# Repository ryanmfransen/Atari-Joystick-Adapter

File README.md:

# Atari Joystick Adapter
A bluetooth adapter for the Atari CX-40 joysticks

## Finished Product

## Design Objectives
You might ask why I would build such a project. With the proliferation of existing gamepads, retro tech, and alternatives, what is it about this that makes it unique?

Fair question. To begin, let's roll back the clock. I used to have all the old systems, and when I wanted to play any of the retro machines, I would simply toss in the cartridge and play away, just like when I was a kid.

I've since sold my collection of retro game machines and recently got into emulation. Emulation affords me the opportunity to still play the old school games yet be able to do so on a single, modern appliance. 

This is great, except for one thing; The joysticks.

I miss playing games as they were intended. It just isn't the same thing playing Space Invaders on the Atari 2600 with the classic joystick as it is playing it on an emulator with a modern XBox controller.  Yes, it works fine, but the experience is not the same.

The Atari Joystick Adapter was born. *I wanted a way to use my classic joysticks the way the games were designed for while playing emulation.*
## Design Goals
**Classic Joysticks**

I wanted to be able to use my existing class joysticks without modification.

**Wireless**

The adapter needed to be wireless, so I can sit back on my couch and play games without being tethered to an appliance.

**Emulator Navigation**

I needed ther ability to navigater, and control the emulator with the classic joystick such that I could select, launch and play games without the use of another controller, remote, or keyboard.

**Additional Game System Buttons**

I needed the ability to mimic the buttons on the original Atari to begin playing games - Start for example.

**Battery Operated**

To be truly wireless, I needed to make this a battery operated device, and be able to charge the device simply by plugging in a USB-C cable such as is with modern rechargeable devices.

**Professional**

Yeah yeah I know, this is a one off device but I want it to look professional, with a custom PCB, and a good looking multicolour 3D printed enclosure.

## The PCB

I designed the circuit using KiCad. I designed most of the symbols, and footprints, sans the simple capacitor, resistor, and connectors. I think I also grabbed the ESP32 symbol from somewhere. The schematics and the KiCad project files can be found here: [Atari Joystick Adapter KiCad Project](kicad/)

Schematic:

Here is a 3d Render (v1.1):

Here is a picture of the populated board (v1.0)

I sent the gerber files to PCBWay to be built, and received 10 boards in about a week.

## Interfacing the Atari Joystick

The Atari joystick uses a simple mechanism to manage the four direction buttons and the fire button.  Each button is assigned to a pin on the connector, and when pressed brings the pin low, as is seen from the ground, or common pin on the connector, pin eight(8). This makes it quite easy to connect to the ESP32, all I needed was simple debounce circuits and can otherwise go straight into the digital GPIO pins.

## The Atari Connector

I recall back in the seventies and eighties we used to use standard DB9 serial connectors when we were making Atari style joysticks or interfacing to them. While these don't quite fit perfectly, they do work well. For this project I wanted to finally make use of real Atari joystick connectors, so I found a source for them in San Jose, Best Electronics, and bough 20 of them.

I've also modelled the Atari joystick connector in CAD.  Mostly just to help facilitate designing the enclosure for fitment, however I also added it to the KiCad footprint so you could also render the 3d model of the PCB with it as well.

You can download the model here: [Atari Joystick Connector Model](models/atarijoystickmodel.step)

## ESP32

I ended up using the ESP32 Mini WROOM-32 by KeeYees.  I really like the mini board configuration, as I have used several of the similar D1Minis ESP8266's in the past.

The ESP32 dev board was the obvious choice for this project as it has the bluetooth connectivity I need and sufficient GPIO pins.

I used this ESP32 from Amazon: [ESP32 Mini Wroom-32](https://www.amazon.ca/gp/product/B08TBQRMY4)

## Battery and Battery Charging

One of my design goals was to use a rechargeable battery and circuit.  I had a bunch of 18650 batteries around for other projects, so that seemed like it would be a good fit for this project.  I would have to settle on a charging circuit, and I could obtain a TC4056 Lithium Battery Charger Module Board from Amazon for quite cheap.  This would more than suffice for what I needed.  The ESP32 uses a 5V input, so I needed to deal with this, as the 18650 has a 3.7v output, which does diminish during it's charge/release cycle.  A simple DC-DC 6W Mini Step-Up Boost Converter would do the trick, and boost me up to 5V, regardless of the diminishing voltage. Perfect - Both these parts are cheap and easily available.

At this point all I had to do was throw a switch into the power circuit and that should solve my power requirements. Done.

I purchased this [Battery Charger](https://www.amazon.ca/gp/product/B0B48VWHTD) from Amazon

I purchased this [Boost Converter](https://www.amazon.ca/gp/product/B09TZSGHYK) from Amazon

## Enclosure

I designed the enclosure in Autodesk's Fusion 360. I think it worked out quite well.  The enclosure consists of the main(top) piece, and the cover (bottom) as well as three switch extensions so you can use the three switches placed in the PCB such that they would extend the proper amount up and out of the top case.

The enclosure CAD files can be found here: [Atari Joystick Adapter CAD Files](models)

The Bambu Studio .3mf file for the enclosure can be found here: [Atari Joystick Adapter Bambu Studio 3mf Project File](bambustudio/Atari%20Joystick%20Adapter%20Case.3mf)

## The Code

I built the code for this project in C++ using Visual Studio Code and PlatformIO, with the Arduino Framework.  I make use the GamepadBLE library by lemmingDEV, found here: [ESP-32-BLE-Gamepad](https://github.com/lemmingDev/ESP32-BLE-Gamepad)

I use a number of classes to manage the program.  The main class is the Button class.  The Button class encapsulates everything needed to support using buttons on your retro joysticks. It will store the current button state, whether the state has changed, which ESP32 GPIO pin the button is assigned to, and it handles the hardware interrupt callback for that button.  Each button manages it's own interup handler to encapsulate the interrupt logic. This class is used for the joystick, or d-pad (hat) direction buttons.

The second Class is the FireButton class, extending the Button class.  This adds in the addition of a button identifier, used for gamepad buttons, such as the fire button.

The interrupt service routines, in the button objects simply set the updated state, and flag the button as having changed state.

Managing the interrupt handler in each object is a handy way to control state. Most solutions I have seen out on Youtube have some sort of global variables storing the state for all the buttons.  I like the ability to do this atomically, it keeps things clean.

Here is the Button class initializer function, setting the ISR for the class instance.
```
void Button::init() {
  // Set the pin to input and use a pullup resistor
  pinMode(pin, INPUT_PULLUP);

  // Set the current state of the pin
  this->state = LOW;

  // Let's attach the interrupt handler
  std::function<void(void)> stdFunct {std::bind(&Button::instanceIsr, this)};
  attachInterrupt(digitalPinToInterrupt(this->pin), stdFunct, CHANGE);
}
```

The main loop of the application simply iterates over the button instances, checking if they have changed state.  If they have, then the new state is sent via the bluetooth gamepad.

The project code and all source files are included for you.

This project was built to accommodate the four joystick direction buttons, the single joystick fire button, as well as three additional buttons to support game system and emulator navigation and control.

The joystick direction buttons are mapped to the four hat buttons in the gamepad emulation.  The possible states are:

```
  LEFT_UP:8     UP:1          UP_RIGHT:2 
  ⎡    ▲    ⎤   ⎡    ▲    ⎤   ⎡    ▲    ⎤
  ⎢    0    ⎟   ⎢    0    ⎟   ⎢    0    ⎟
  ⎢◀︎ 0   1 ▷⎟   ⎢◁ 1   1 ▷⎟   ⎢◁ 1   0 ▶︎⎟
  ⎢    1    ⎟   ⎢    1    ⎟   ⎢    1    ⎟ 
  ⎣    ▽    ⎦   ⎣    ▽    ⎦   ⎣    ▽    ⎦ 
  
  LEFT:7        CENTERED:0    RIGHT:3
  ⎡    △    ⎤   ⎡    △    ⎤   ⎡    △    ⎤
  ⎢    1    ⎟   ⎢    1    ⎟   ⎢    1    ⎟
  ⎢◀︎ 0   1 ▷⎟   ⎢◁ 1   1 ▷⎟   ⎢◁ 1   0 ▶︎⎟
  ⎢    1    ⎟   ⎢    1    ⎟   ⎢    1    ⎟
  ⎣    ▽    ⎦   ⎣    ▽    ⎦   ⎣    ▽    ⎦
  
  DOWN_LEFT:6   DOWN:5        DOWN_RIGHT:4
  ⎡    △    ⎤   ⎡    △    ⎤   ⎡    △    ⎤
  ⎢    1    ⎟   ⎢    1    ⎟   ⎢    1    ⎟ 
  ⎢◀︎ 0   1 ▷⎟   ⎢◁ 1   1 ▷⎟   ⎢◁ 1   0 ▶︎⎟
  ⎢    0    ⎟   ⎢    0    ⎟   ⎢    0    ⎟
  ⎣    ▼    ⎦   ⎣    ▼    ⎦   ⎣    ▼    ⎦
```
Each state is mapped to an integer value, from `0..8` and it is this integer value sent to the gamepad controller to register the d-pad presses in the emulator.

The four buttons are buttons `1..4`, and are typically registered, depending on the system you pair with, as buttons a, b, x, y on the gamepad controller in the emulator.

From here, you can assign each of these four buttons to whatever makes sense for you.  I used:
```
[a], [b], [select], [start]
```

## Emulator

I use Retroarch, and it was a little tricky getting the proper button assignments configured so I could navigate the Retroarch menu, launch the game in the emulator, and then start the game, and play the game all with only using the Atari joystick and the buttons on the adapter.

Once configured, it works incredibly well.

## Did I achieve my Goals?

Yes! I believe so. Let's have a look:
- [x]  Classic Joysticks
- [x]  Wireless
- [x]  Emulator Navigation
- [x]  Additional Game System Buttons
- [x]  Battery Operated
- [x]  Professional

## Observations

1. Latency.  The latency is either incredible, or I am blind to it because I put so much effort into making this. In any event, gameplay is amazing, and very responsive.  I am very happy with the latency given the bluetooth connectivity, and emulation.

2. I actually use this.  Unlike most of my projects which are super fun to build, they usually end up on a shelf, or in a drawer, and I tend to forget about them. This project is different.  I actually is it, and is a lot of fun to play the games wit hthe classic controllers.

## What I Would do Different Next Time

1. Test Points. I would (and have in the v2 board) include test points to troubleshoot the circuit. This just makes things much easier to measure voltages and test your circuits.

2. Power Jumper. Ok, so I have to admit I placed all the parts, soldered everything in, and powered it on.  Of course, I forgot to configure the voltage booster from the default 12v to my required 5v, and I fried my brand new ESP32. 
 I've since added a two pin jumper that needs to be in place for the power to get to the ESP32, this way I can power the board up and test the circuit power without destroying the ESP.

3. My first prototype had the ESP32 soldered directly to the board, and while offers a nice finished product, see point 2 above, and I needed to remove it, so prototype two I put headers in and as you can see from the picture, the ESP32 is now removable, if ever needed.

4. While the 18650 works well, I might source a small flat pack lithium ion battery. The package is much smaller and will have plenty of power for what I need.  Would also remove the need for the battery holder I had to source.

## Next Steps

1. Driving Controller. I would like to support the Atari driving controller used for games like Indy 500.

2. Paddle Controllers. I would also like to support the Atari paddle controllers used for games like Super Breakout or Warlords.

3. Sega or Nintendo Controllers. Might be nice to extend this to use the controllers using shift registers or other multiplexers. Modern versions of these controllers can be purchased, so uncertain about this.

4. Two Player support. At the moment, this is a device for a single Atari joystick. Perhaps I could extend this to support two joysticks for two player games without requiring two devices.

## Contact Me!

If you would like to discuss the project or have an idea, or question please reach out.  I can be reached at:

`ryan.fransen[the symbol for at]me.com`

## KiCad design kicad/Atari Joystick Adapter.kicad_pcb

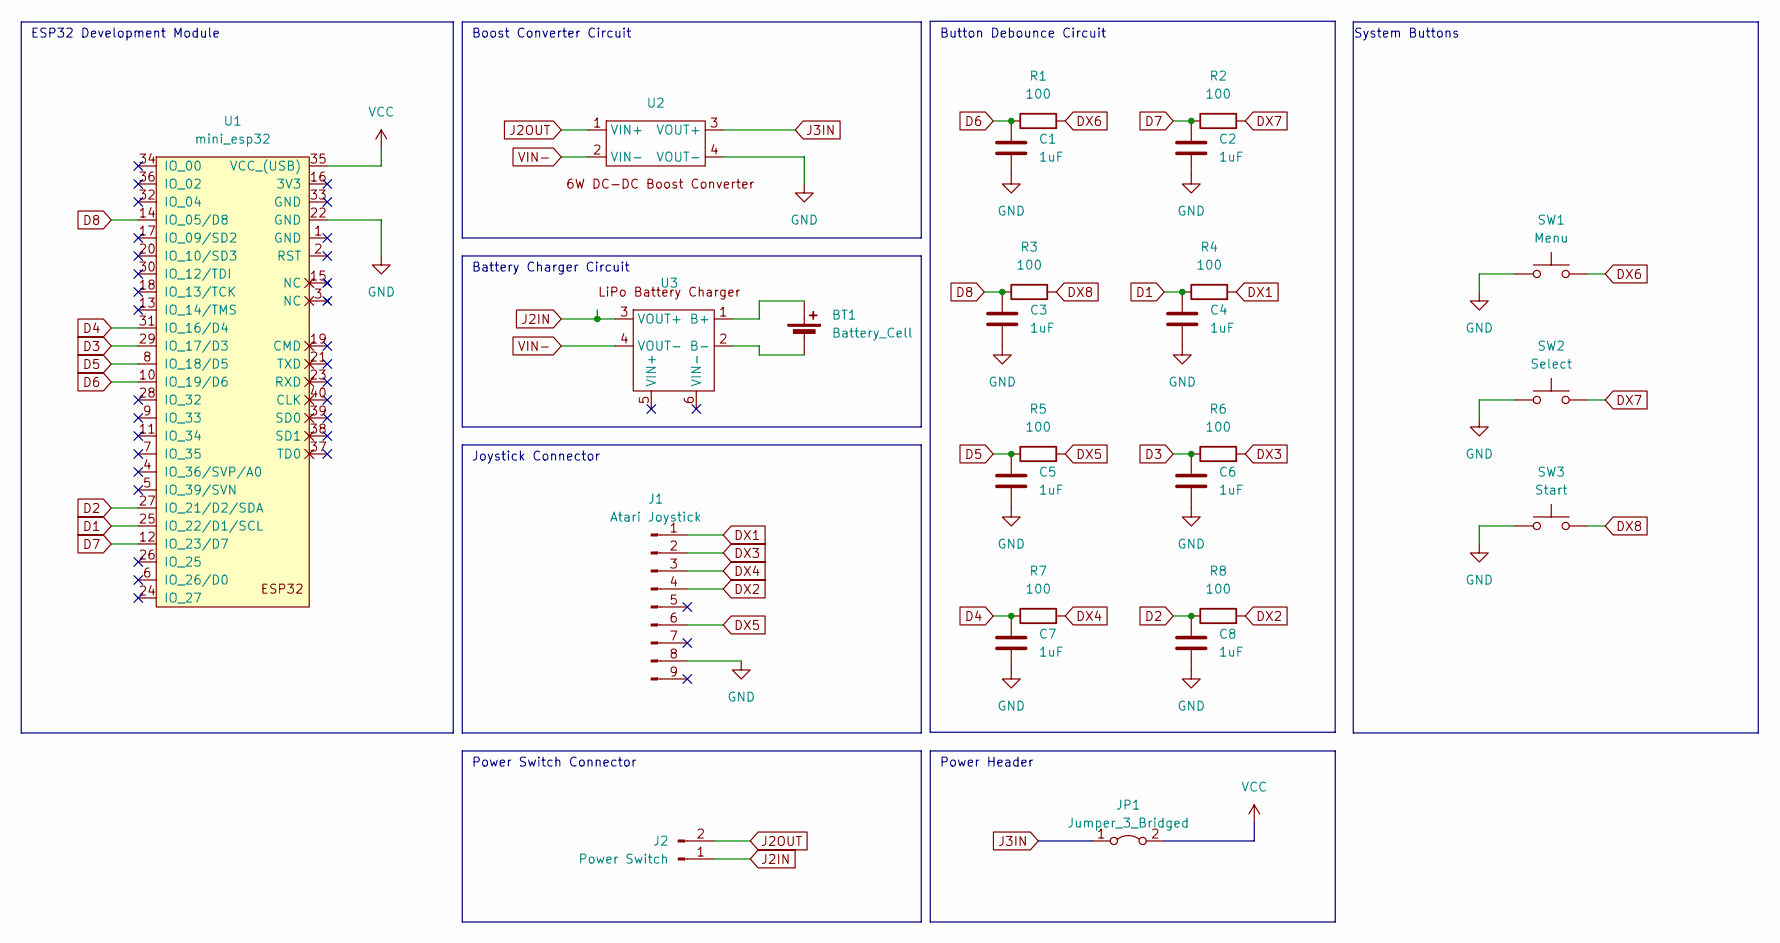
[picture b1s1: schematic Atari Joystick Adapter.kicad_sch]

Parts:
BT1: Battery_Cell; BatteryHolder_BH-18650
C1, C2, C3, C4, C5, C6, C7, C8: 1uF; C_Disc_D4.3mm_W1.9mm_P5.00mm
J1: Atari Joystick; Atari 9Pin Joystick Connector
J2: Power Switch; JST_EH_B2B-EH-A_1x02_P2.50mm_Vertical
JP1: Jumper_3_Bridged; PinSocket_1x02_P2.54mm_Vertical
R1, R2, R3, R4, R5, R6, R7, R8: 100; R_Axial_DIN0207_L6.3mm_D2.5mm_P10.16mm_Horizontal
SW1: Menu; SW_PUSH-12mm
SW2: Select; SW_PUSH-12mm
SW3: Start; SW_PUSH-12mm
U1: mini_esp32; ESP32_mini
U2: 6W DC-DC Boost Converter
U3: LiPo Battery Charger Circuit

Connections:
D1: C4.1, R4.1, U1.25 (IO_22/D1/SCL)
D2: C8.1, R8.1, U1.27 (IO_21/D2/SDA)
D3: C6.1, R6.1, U1.29 (IO_17/D3)
D4: C7.1, R7.1, U1.31 (IO_16/D4)
D5: C5.1, R5.1, U1.8 (IO_18/D5)
D6: C1.1, R1.1, U1.10 (IO_19/D6)
D7: C2.1, R2.1, U1.12 (IO_23/D7)
D8: C3.1, R3.1, U1.14 (IO_05/D8)
DX1: J1.1, R4.2
DX2: J1.4, R8.2
DX3: J1.2, R6.2
DX4: J1.3, R7.2
DX5: J1.6, R5.2
DX6: R1.2, SW1.2
DX7: R2.2, SW2.2
DX8: R3.2, SW3.2
GND: C1.2, C2.2, C3.2, C4.2, C5.2, C6.2, C7.2, C8.2, J1.8, SW1.1, SW2.1, SW3.1, U1.22 (GND), U2.4 (VOUT-)
J2IN: J2.1, U3.3 (VOUT+)
J2OUT: J2.2, U2.1 (VIN+)
J3IN: JP1.1 (A), U2.3 (VOUT+)
unnamed: BT1.1 (+), U3.1 (B+)
unnamed: BT1.2 (-), U3.2 (B-)
VCC: JP1.2 (B), U1.35 (VCC_(USB))
VIN-: U2.2 (VIN-), U3.4 (VOUT-)

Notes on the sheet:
Button Debounce Circuit
ESP32 Development Module
System Buttons
Boost Converter Circuit
Power Header
Battery Charger Circuit
Joystick Connector
Power Switch Connector

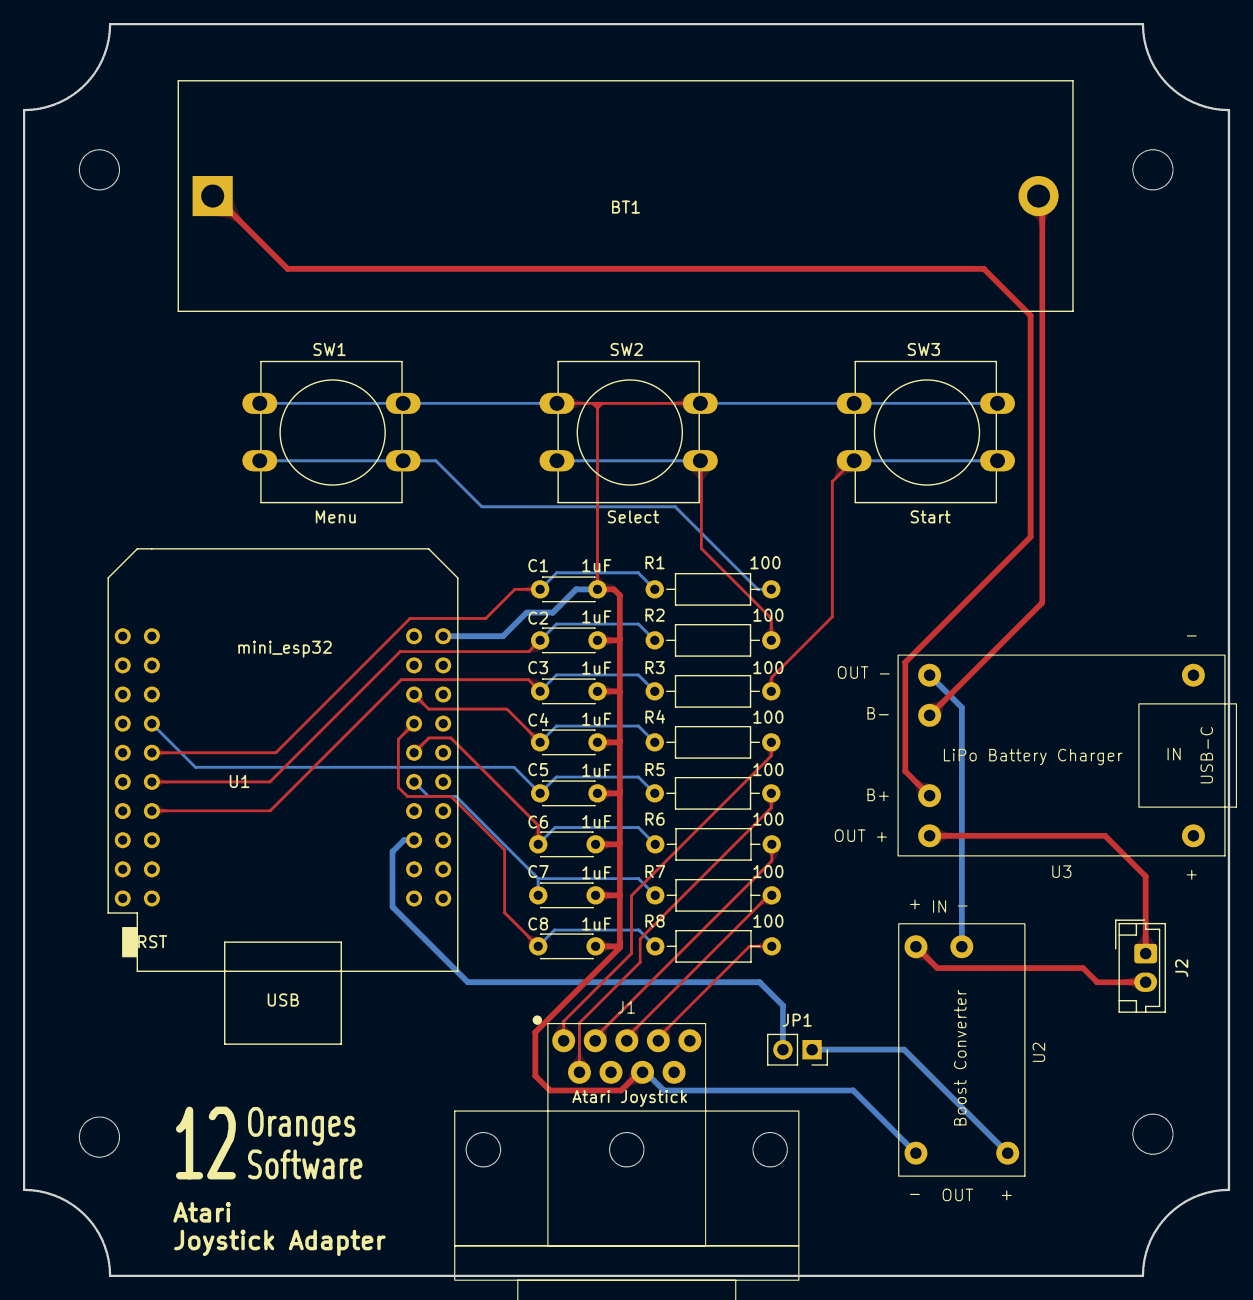
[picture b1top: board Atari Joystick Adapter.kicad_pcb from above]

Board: 2 copper layers, 105.0 x 109.1 mm, 30 parts (0 on the bottom side), 24 nets.

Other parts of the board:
H1, H2, H3, H4: MountingHole; MountingHole_3.5mm

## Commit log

2024-03-30 Initial commit.
2024-03-30 Updated links in readme for updated structure.
2024-03-30 Updated readme with pcb and esp32 info.
2024-03-30 Updated readme with enclosure render.
2024-03-30 Updated readme with enclosure info.
2024-03-30 Readme update.
2024-03-30 doc update.
2024-03-30 img size.
2024-03-30 Removed unnecessary dep.
